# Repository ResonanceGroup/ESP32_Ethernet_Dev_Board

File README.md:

This project is meant to test 2 different ethernet controller chips for the ESP32. The board is testing the W5100S and W5500. Only populate one or the other. Feel free to use this schematic as a reference. Or make your dev board that includes the ethernet controllers. If referencing off of the schematic, please provide credit to the original project (this one).

Will update later which circuit performed the best.

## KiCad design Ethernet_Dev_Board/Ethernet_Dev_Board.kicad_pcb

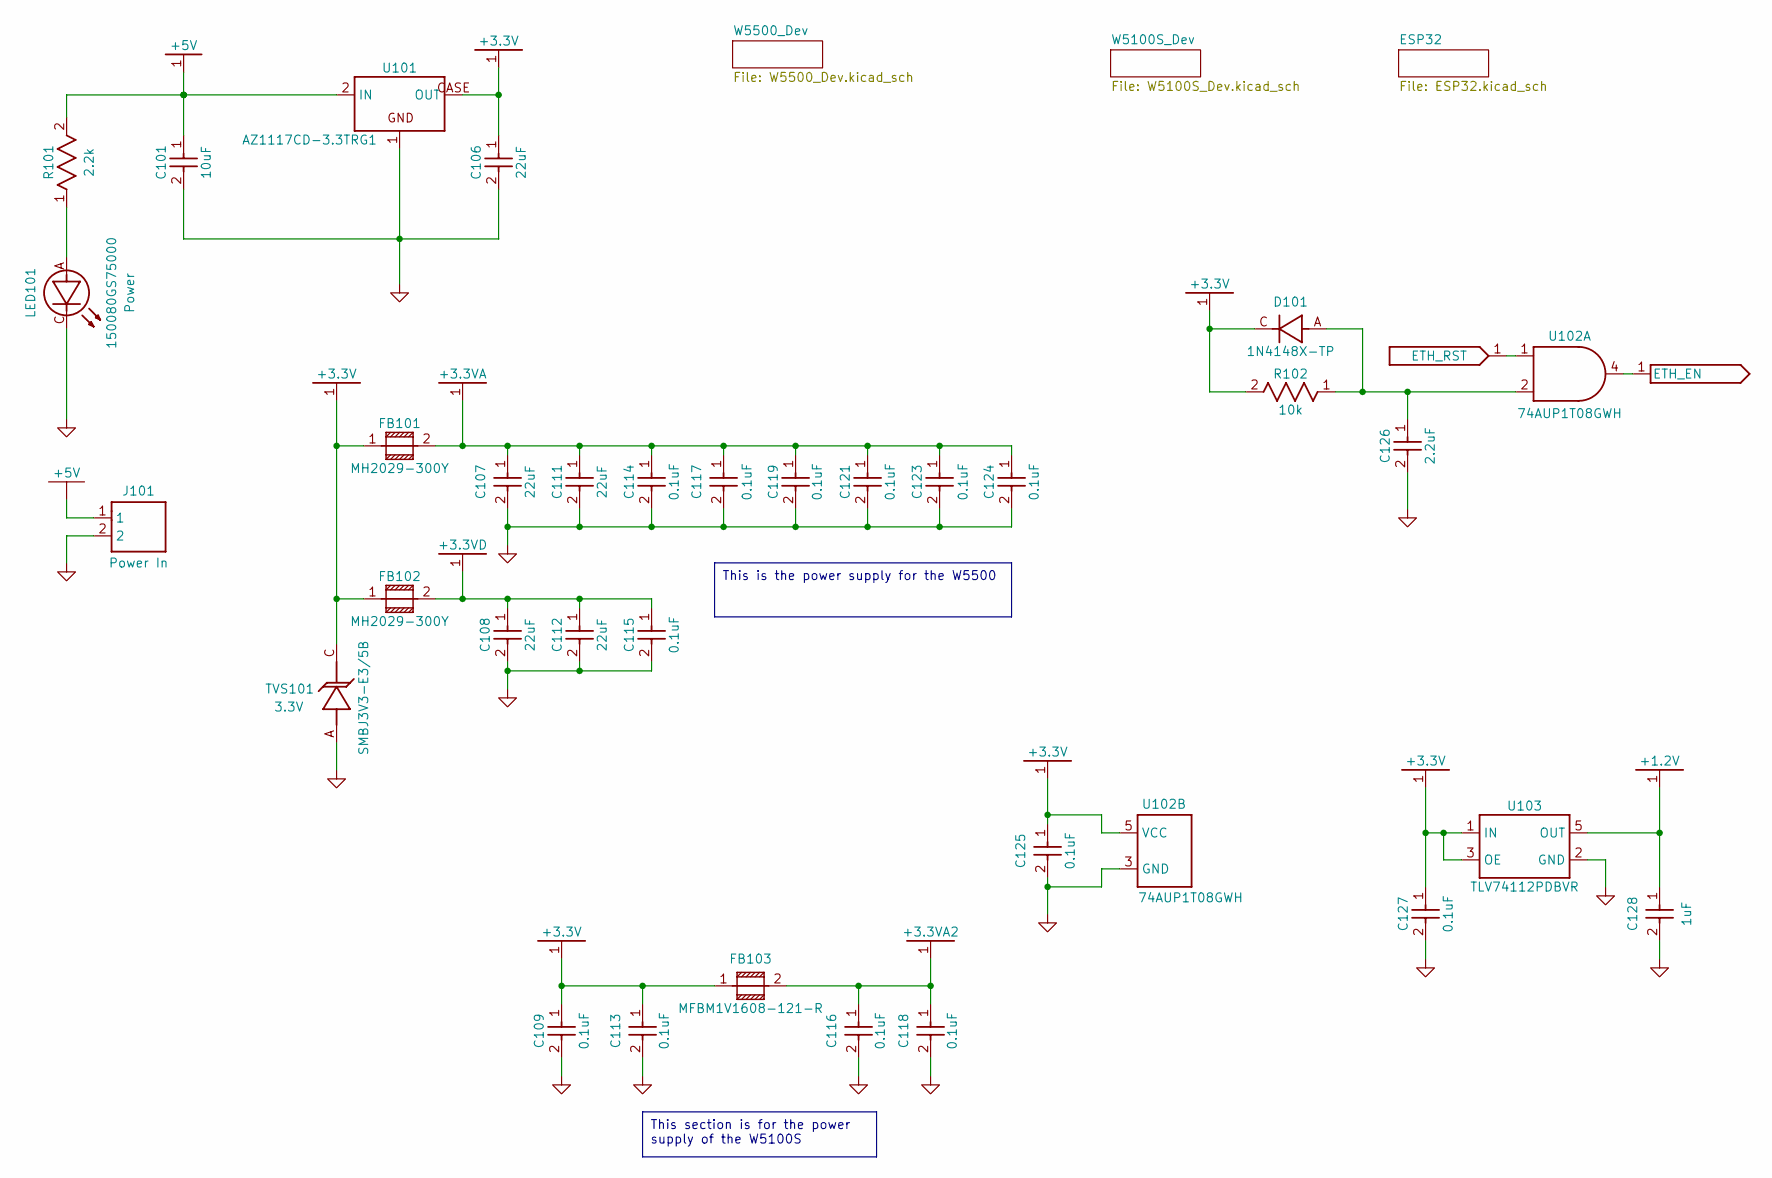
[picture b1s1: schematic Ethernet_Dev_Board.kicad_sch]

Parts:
C101: 10uF; 0603; Mfg. PN GRM188R61C106MA73D
C106, C107, C108, C111, C112: 22uF; 0603; Mfg. PN CL10A226MP8NUNE
C109, C113, C114, C115, C116, C117, C118, C119, C121, C123, C124, C125, C127: 0.1uF; 0603; Mfg. PN TMK107BJ104KA-T
C126: 2.2uF; 0603; Mfg. PN CL10A225KP8NNNC
C128: 1uF; 0603; Mfg. PN CL10B105KP8NFNC
D101: 1N4148X; SOD-523-D; Mfg. PN 1N4148X-TP
FB101, FB102: MH2029-300Y; 0805; Mfg. PN MH2029-300Y
FB103: 0603; Mfg. PN MFBM1V1608-121-R
J101: Power In; CUI_TBP01R1-508-02BE; Mfg. PN TBP01R1-508-02BE
LED101: Power; 0805-D; Mfg. PN 150080GS75000
R101: 2.2k; 0603; Mfg. PN RMCF0603FT2K20
R102: 10k; 0603; Mfg. PN RMCF0603FT10K0
TVS101: 3.3V; SMB-D; Mfg. PN SMBJ3V3-E3/5B
U101: AZ1117; TO252-3_(D-PAK); Mfg. PN AZ1117CD-3.3TRG1
U102: 74AUP1T08GWH; SOT23-5P65; Mfg. PN 74AUP1T08GWH
U103: 1.2V; SOT23-5P65; Mfg. PN TLV74112PDBVR

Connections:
+1.2V: C128.1, U103.5 (OUT); also elsewhere on the board
+3.3V: C106.1, C109.1, C113.1, C125.1, C127.1, D101.C, FB101.1, FB102.1, FB103.1, R102.2, TVS101.C (2), U101.CASE (OUT), U102.5 (VCC), U103.1 (IN), U103.3 (OE); also elsewhere on the board
+3.3VA: C107.1, C111.1, C114.1, C117.1, C119.1, C121.1, C123.1, C124.1, FB101.2; also elsewhere on the board
+3.3VA2: C116.1, C118.1, FB103.2; also elsewhere on the board
+3.3VD: C108.1, C112.1, C115.1, FB102.2; also elsewhere on the board
+5V: C101.1, J101.1, R101.2, U101.2 (IN); also elsewhere on the board
ETH_EN: U102.4 (Y); also elsewhere on the board
ETH_RST: U102.1 (A); also elsewhere on the board
GND1: C101.2, C106.2, C107.2, C108.2, C109.2, C111.2, C112.2, C113.2, C114.2, C115.2, C116.2, C117.2, C118.2, C119.2, C121.2, C123.2, C124.2, C125.2, C126.2, C127.2, C128.2, J101.2, LED101.C, TVS101.A (1), U101.1 (GND), U102.3 (GND), U103.2 (GND); also elsewhere on the board
unnamed: LED101.A, R101.1
unnamed: C126.1, D101.A, R102.1, U102.2 (C)

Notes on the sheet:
This is the power supply for the W5500
This section is for the power supply of the W5100S

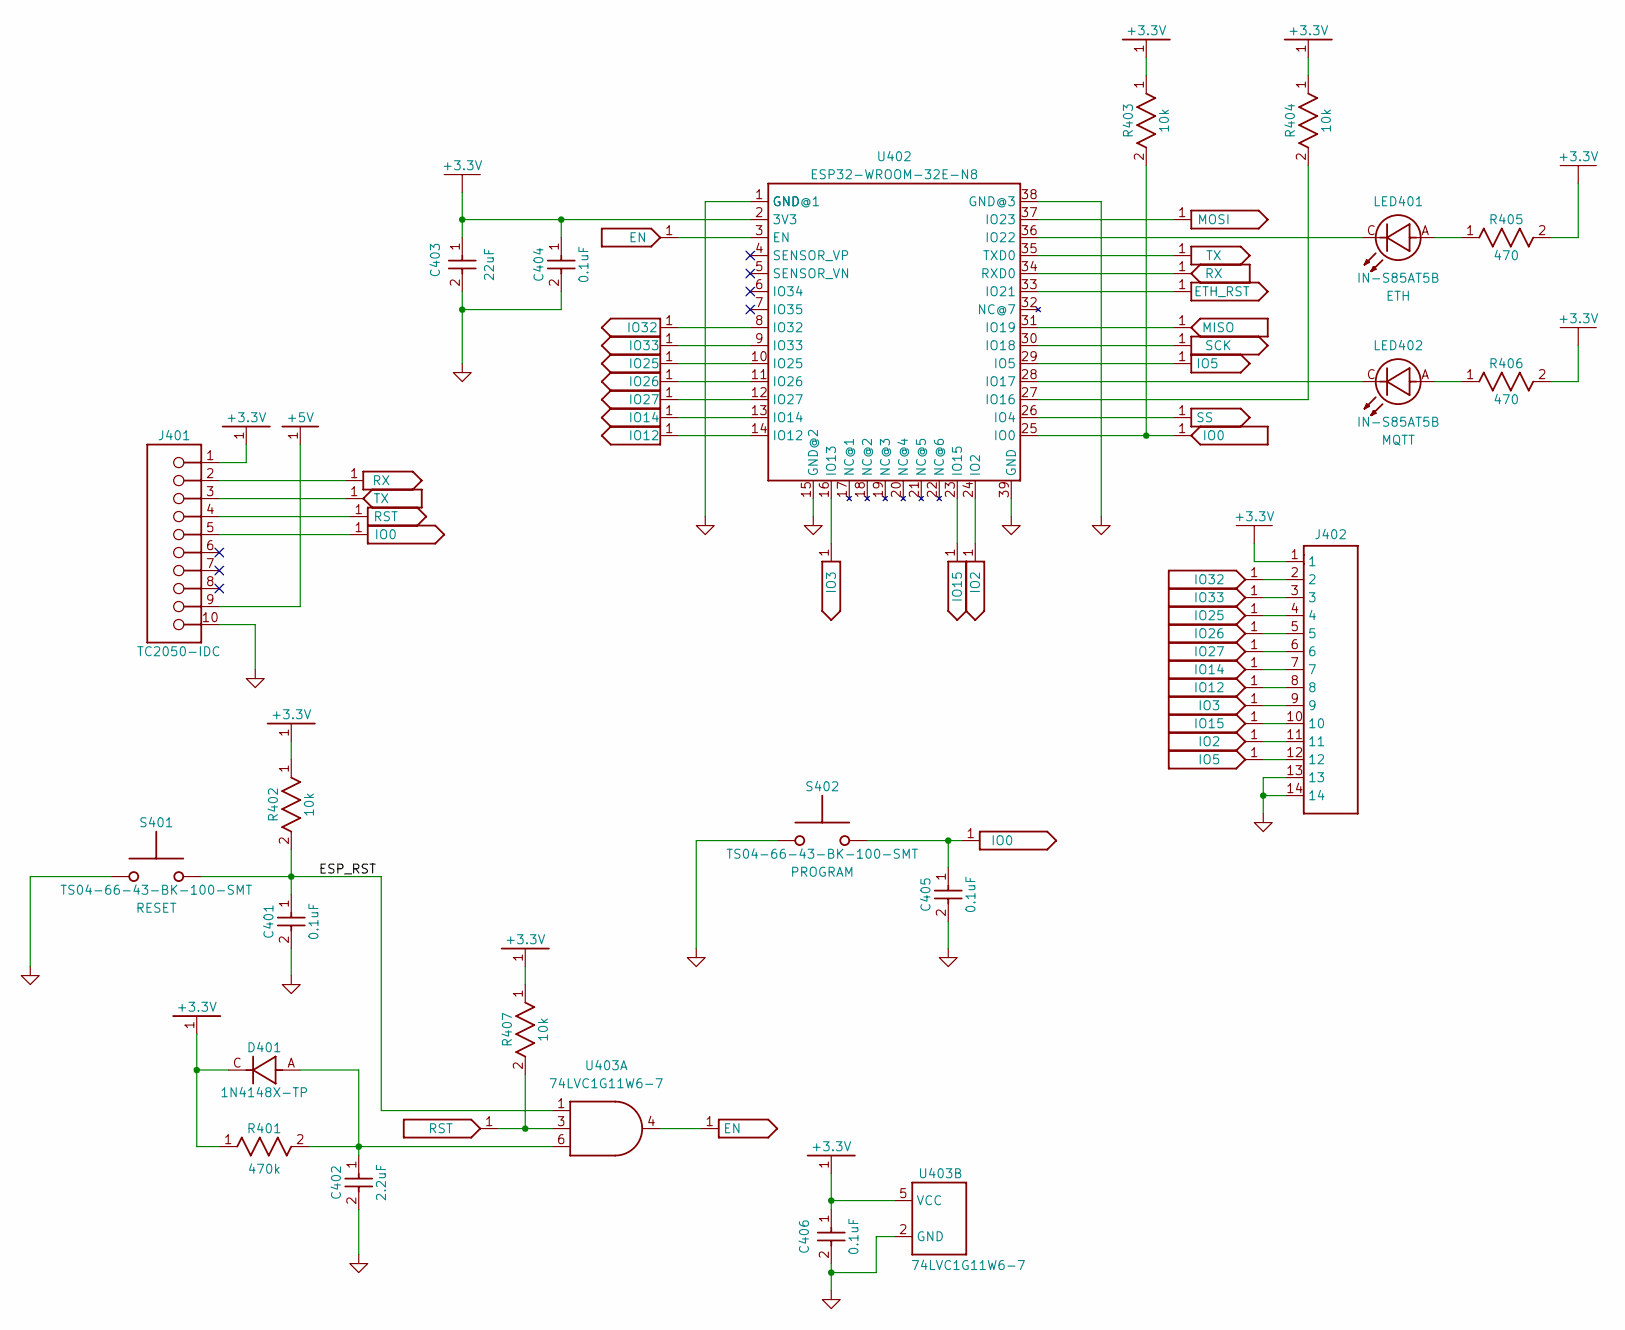
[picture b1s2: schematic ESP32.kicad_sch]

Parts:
C401, C404, C405, C406: 0.1uF; 0603; Mfg. PN TMK107BJ104KA-T
C402: 2.2uF; 0603; Mfg. PN CL10A225KP8NNNC
C403: 22uF; 0603; Mfg. PN CL10A226MP8NUNE
D401: 1N4148X; SOD-523-D; Mfg. PN 1N4148X-TP
J401: TAG-CONNECT_NL_10-POS_LEGS; TC2050-IDC; Mfg. PN TC2050-IDC
J402: PinHeader_1x14_P2.54mm_Vertical
LED401: ETH; 0805-D; Mfg. PN IN-S85AT5B
LED402: MQTT; 0805-D; Mfg. PN IN-S85AT5B
R401: 470k; 0603; Mfg. PN RMCF0603FT470K
R402, R403, R404, R407: 10k; 0603; Mfg. PN RMCF0603FT10K0
R405, R406: 470; 0603; Mfg. PN RMCF0603FT470R
S401: RESET; SW_TS04-66-65-BK-260-SMT; Mfg. PN TS04-66-43-BK-100-SMT
S402: PROGRAM; SW_TS04-66-65-BK-260-SMT; Mfg. PN TS04-66-43-BK-100-SMT
U402: ESP32-WROOM-32E; ESP32-WROOM_PCBANT; Mfg. PN ESP32-WROOM-32E-N8
U403: 74LVC1G11W6; SOT23-6; Mfg. PN 74LVC1G11W6-7

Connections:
+3.3V: C403.1, C404.1, C406.1, D401.C, J401.1, J402.1, R401.1, R402.1, R403.1, R404.1, R405.2, R406.2, R407.1, U402.2 (3V3), U403.5 (VCC); also elsewhere on the board
+5V: J401.9; also elsewhere on the board
/ESP32/ESP_RST: C401.1, R402.2, S401.1 (2), S401.3 (2), U403.1 (A)
EN: U402.3 (EN), U403.4 (Y)
ETH_RST: U402.33 (IO21); also elsewhere on the board
GND1: C401.2, C402.2, C403.2, C404.2, C405.2, C406.2, J401.10, J402.13, J402.14, S401.2 (1), S401.4 (1), S402.2 (1), S402.4 (1), U402.1 (GND), U402.15 (GND@2), U402.38 (GND@3), U402.39 (GND), U403.2 (GND); also elsewhere on the board
IO0: C405.1, J401.5, R403.2, S402.1 (2), S402.3 (2), U402.25 (IO0)
IO2: J402.11, U402.24 (IO2)
IO3: J402.9, U402.16 (IO13)
IO5: J402.12, U402.29 (IO5)
IO12: J402.8, U402.14 (IO12)
IO14: J402.7, U402.13 (IO14)
IO15: J402.10, U402.23 (IO15)
IO25: J402.4, U402.10 (IO25)
IO26: J402.5, U402.11 (IO26)
IO27: J402.6, U402.12 (IO27)
IO32: J402.2, U402.8 (IO32)
IO33: J402.3, U402.9 (IO33)
MISO: U402.31 (IO19); also elsewhere on the board
MOSI: U402.37 (IO23); also elsewhere on the board
unnamed: LED401.A, R405.1
unnamed: LED402.A, R406.1
unnamed: R404.2, U402.27 (IO16)
unnamed: LED402.C, U402.28 (IO17)
unnamed: LED401.C, U402.36 (IO22)
unnamed: C402.1, D401.A, R401.2, U403.6 (C)
RST: J401.4, R407.2, U403.3 (B)
RX: J401.2, U402.34 (RXD0)
SCK: U402.30 (IO18); also elsewhere on the board
SS: U402.26 (IO4); also elsewhere on the board
TX: J401.3, U402.35 (TXD0)

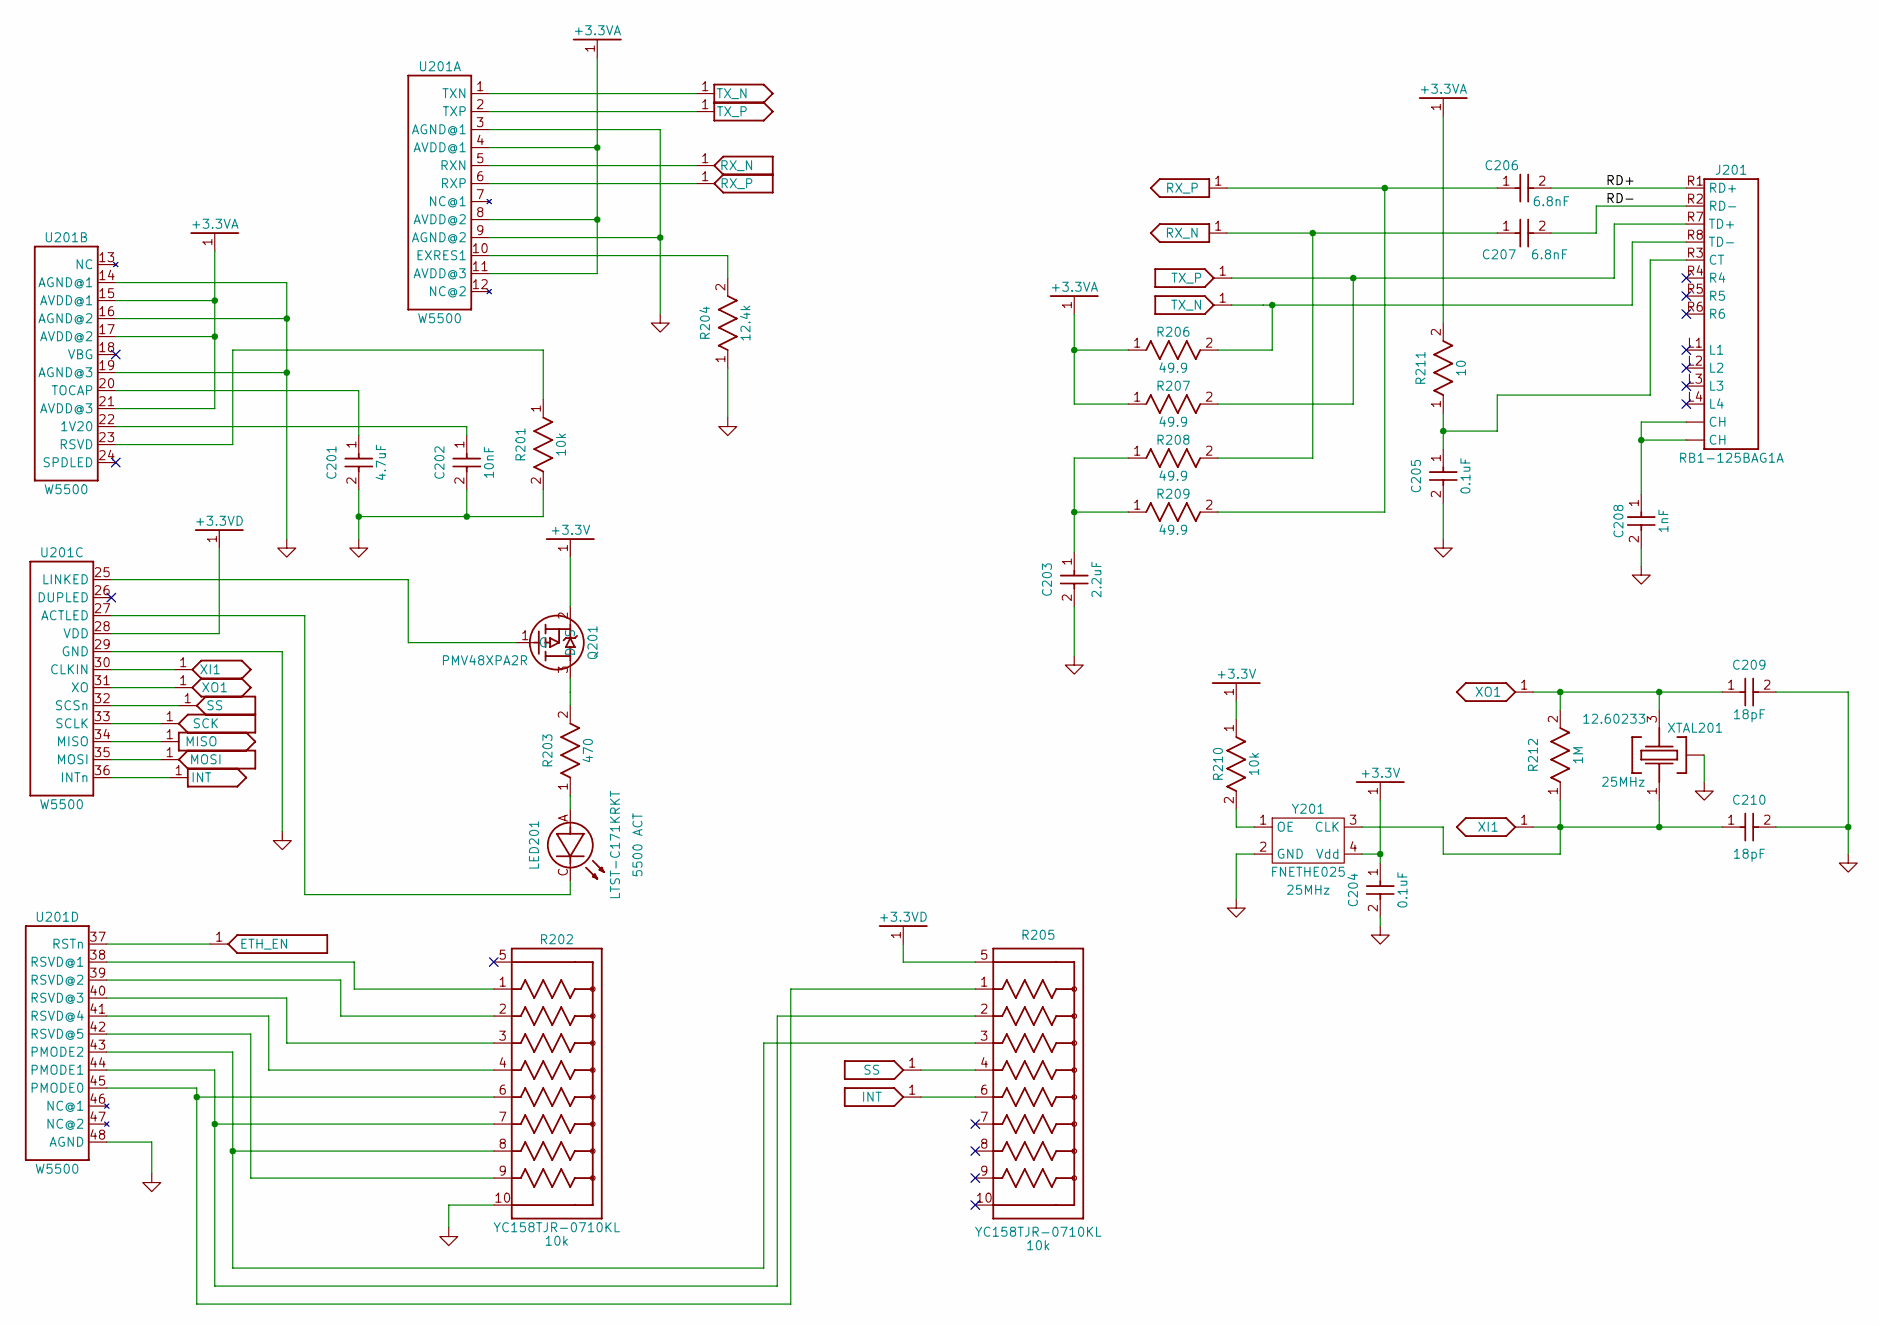
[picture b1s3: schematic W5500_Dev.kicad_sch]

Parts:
C201: 4.7uF; 0603; Mfg. PN CL10A475KP8NNNC
C202: 10nF; 0603; Mfg. PN GRM1885C1H103JA01J
C203: 2.2uF; 0603; Mfg. PN CL10A225KP8NNNC
C204, C205: 0.1uF; 0603; Mfg. PN TMK107BJ104KA-T
C206, C207: 6.8nF; 0603; Mfg. PN C1608C0G2A682J080AC
C208: 1nF; 1206; Mfg. PN C1206C102KGRAC7800
C209, C210: 18pF; 0603; Mfg. PN CML0603C0G180JT50V
J201: WIZNET_RB1-125BAG1A; Mfg. PN RB1-125BAG1A
LED201: 5500 ACT; 0805-D; Mfg. PN LTST-C171KRKT
Q201: PMV48XPA2R; SOT23-3P95; Mfg. PN PMV48XPA2R
R201, R210: 10k; 0603; Mfg. PN RMCF0603FT10K0
R202, R205: 10k; RESCAXS10P64_1206; Mfg. PN YC158TJR-0710KL
R203: 470; 0603; Mfg. PN RMCF0603FT470R
R204: 12.4k; 0603; Mfg. PN RMCF0603FT12K4
R206, R207, R208, R209: 49.9; 0603; Mfg. PN RMCF0603FT49R9
R211: 10; 0603; Mfg. PN RMCF0603FT10R0
R212: 1M; 0603; Mfg. PN RMCF0603FG1M00
U201: WIZNET_W5500; QFP48P50; Mfg. PN W5500
XTAL201: 25MHz; YANGXING_SMD_3225_4L; Mfg. PN 12.60233
Y201: 25MHz; Crystal_SMD_4Pin_7.0mmx5.0mm; Mfg. PN FNETHE025

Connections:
+3.3V: C204.1, Q201.2 (S), R210.1, Y201.4 (Vdd); also elsewhere on the board
+3.3VA: R206.1, R207.1, R211.2, U201.4 (AVDD@1), U201.8 (AVDD@2), U201.11 (AVDD@3), U201.15 (AVDD@1), U201.17 (AVDD@2), U201.21 (AVDD@3); also elsewhere on the board
+3.3VD: R205.5 (1@1), U201.28 (VDD); also elsewhere on the board
/W5500_Dev/RD+: C206.2, J201.R1 (RD+)
/W5500_Dev/RD-: C207.2, J201.R2 (RD-)
ETH_EN: U201.37 (RSTn); also elsewhere on the board
GND1: C201.2, C202.2, C203.2, C204.2, C205.2, C208.2, C209.2, C210.2, R201.2, R202.10 (1@2), R204.1, U201.3 (AGND@1), U201.9 (AGND@2), U201.14 (AGND@1), U201.16 (AGND@2), U201.19 (AGND@3), U201.29 (GND), U201.48 (AGND), XTAL201.2 (3@2), Y201.2 (GND); also elsewhere on the board
INT: R205.6, U201.36 (INTn)
MISO: U201.34 (MISO); also elsewhere on the board
MOSI: U201.35 (MOSI); also elsewhere on the board
unnamed: C203.1, R208.1, R209.1
unnamed: C208.1, J201.S1 (CH), J201.S2 (CH)
unnamed: C205.1, J201.R3 (CT), R211.1
unnamed: LED201.A, R203.1
unnamed: Q201.3 (D), R203.2
unnamed: Q201.1 (G), U201.25 (LINKED)
unnamed: R202.1 (2), U201.38 (RSVD@1)
unnamed: R202.2 (3), U201.39 (RSVD@2)
unnamed: R202.3 (4), U201.40 (RSVD@3)
unnamed: R202.4 (5), U201.41 (RSVD@4)
unnamed: R202.6, R205.1 (2), U201.45 (PMODE0)
unnamed: R202.7, R205.2 (3), U201.44 (PMODE1)
unnamed: R202.8, R205.3 (4), U201.43 (PMODE2)
unnamed: R204.2, U201.10 (EXRES1)
unnamed: C202.1, U201.22 (1V20)
unnamed: R201.1, U201.23 (RSVD)
unnamed: C201.1, U201.20 (TOCAP)
unnamed: LED201.C, U201.27 (ACTLED)
unnamed: R202.9, U201.42 (RSVD@5)
unnamed: R210.2, Y201.1 (OE)
RX_N: C207.1, R208.2, U201.5 (RXN)
RX_P: C206.1, R209.2, U201.6 (RXP)
SCK: U201.33 (SCLK); also elsewhere on the board
SS: R205.4 (5), U201.32 (SCSn); also elsewhere on the board
TX_N: J201.R8 (TD-), R206.2, U201.1 (TXN)
TX_P: J201.R7 (TD+), R207.2, U201.2 (TXP)
XI1: C210.1, R212.1, U201.30 (CLKIN), XTAL201.1, Y201.3 (CLK)
XO1: C209.1, R212.2, U201.31 (XO), XTAL201.3 (3@1)

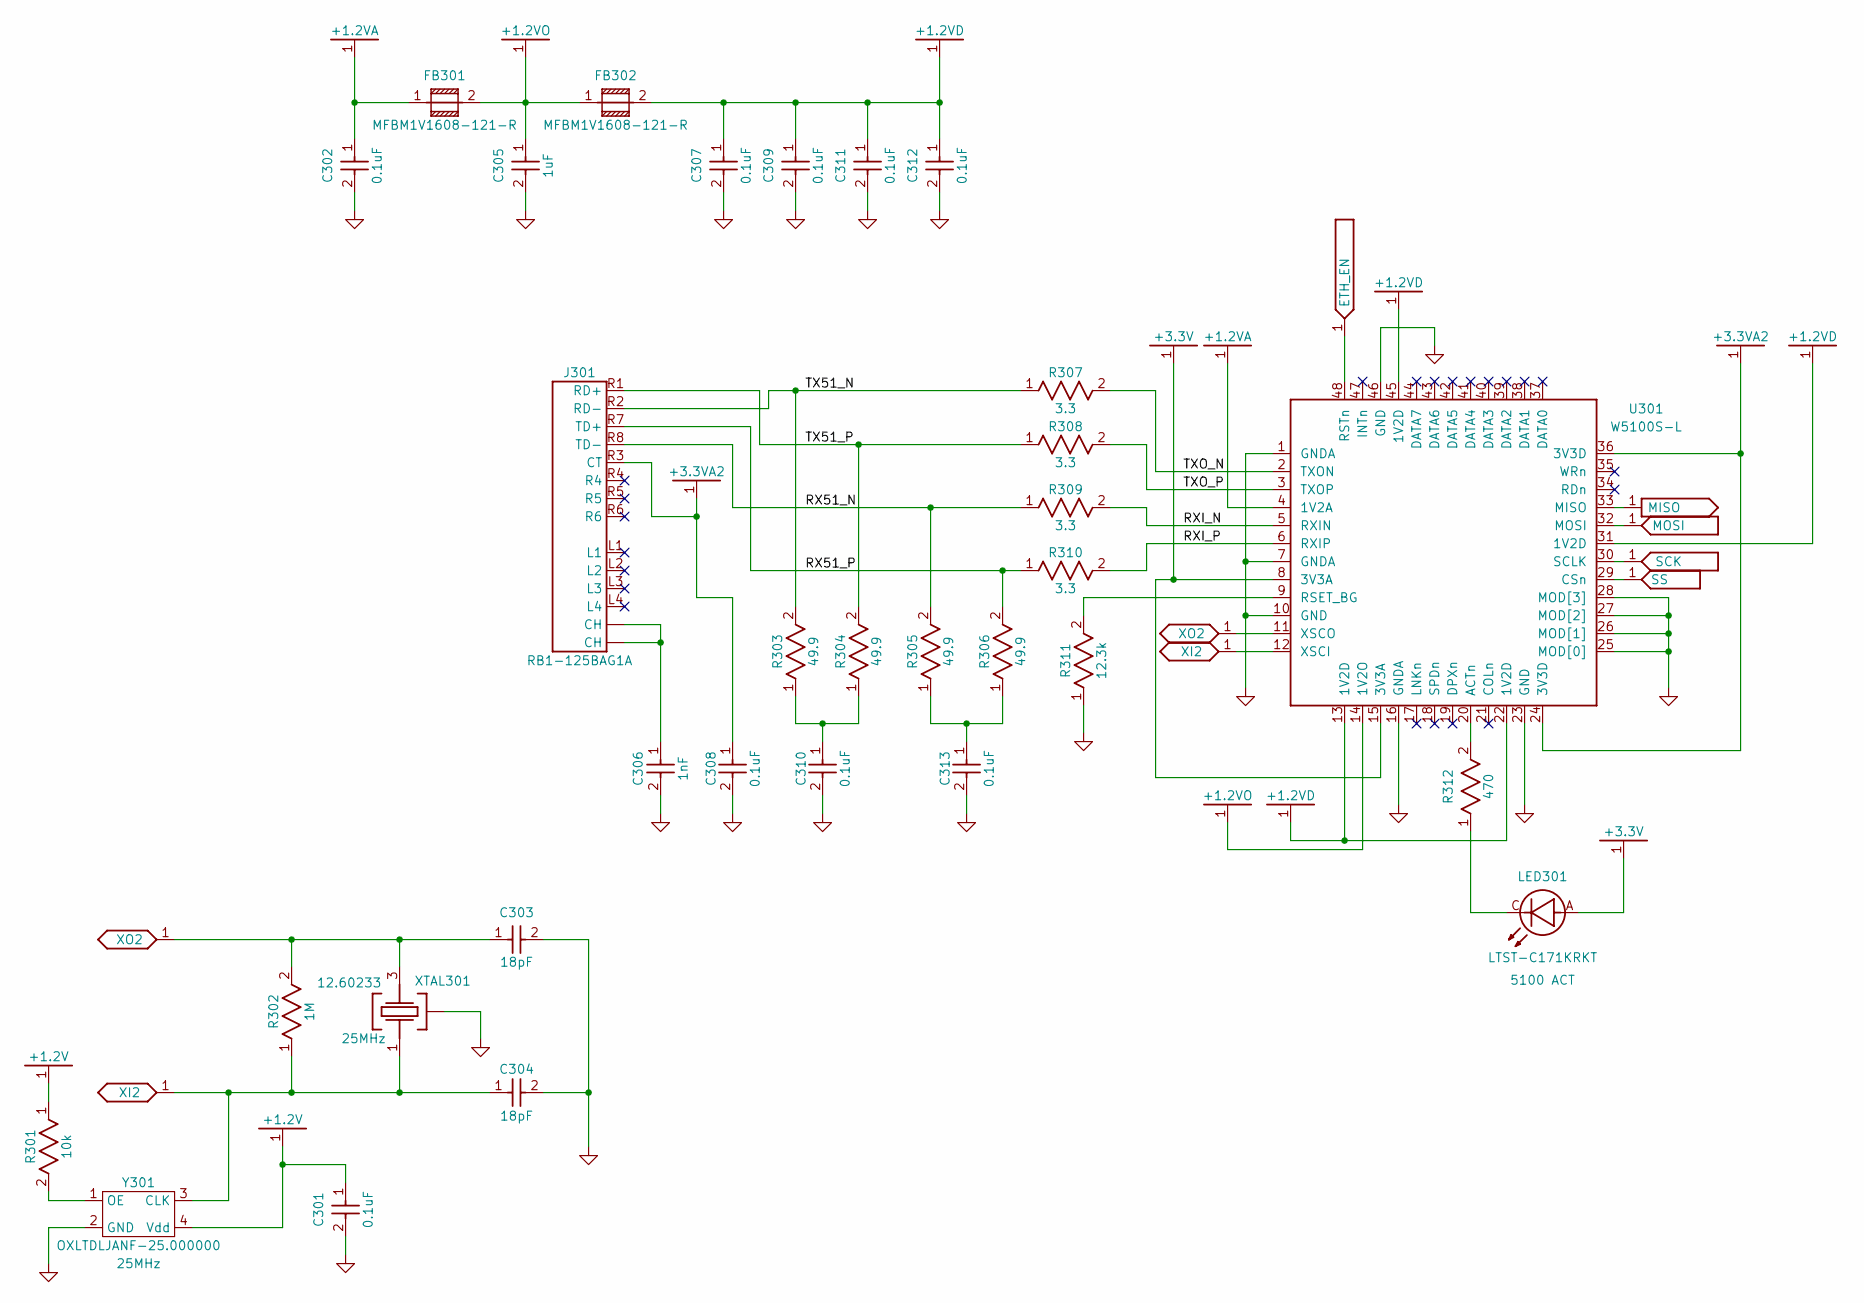
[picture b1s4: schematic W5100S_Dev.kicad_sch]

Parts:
C301, C302, C307, C308, C309, C310, C311, C312, C313: 0.1uF; 0603; Mfg. PN TMK107BJ104KA-T
C303, C304: 18pF; 0603; Mfg. PN CML0603C0G180JT50V
C305: 1uF; 0603; Mfg. PN CL10B105KP8NFNC
C306: 1nF; 1206; Mfg. PN C1206C102KGRAC7800
FB301, FB302: 0603; Mfg. PN MFBM1V1608-121-R
J301: WIZNET_RB1-125BAG1A; Mfg. PN RB1-125BAG1A
LED301: 5100 ACT; 0805-D; Mfg. PN LTST-C171KRKT
R301: 10k; 0603; Mfg. PN RMCF0603FT10K0
R302: 1M; 0603; Mfg. PN RMCF0603FG1M00
R303, R304, R305, R306: 49.9; 0603; Mfg. PN RMCF0603FT49R9
R307, R308, R309, R310: 3.3; 0603; Mfg. PN RMCF0603JT3R30
R311: 12.3k; 0603; Mfg. PN RT0603BRD0712K3L
R312: 470; 0603; Mfg. PN RMCF0603FT470R
U301: QFP48P50; Mfg. PN W5100S-L
XTAL301: 25MHz; YANGXING_SMD_3225_4L; Mfg. PN 12.60233
Y301: 25MHz; Crystal_SMD_4Pin_3.2x2.5mm; Mfg. PN OXLTDLJANF-25.000000

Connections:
+1.2V: C301.1, R301.1, Y301.4 (Vdd); also elsewhere on the board
+1.2VA: C302.1, FB301.1, U301.4 (1V2A)
+1.2VD: C307.1, C309.1, C311.1, C312.1, FB302.2, U301.13 (1V2D), U301.22 (1V2D), U301.31 (1V2D), U301.45 (1V2D)
+1.2VO: C305.1, FB301.2, FB302.1, U301.14 (1V2O)
+3.3V: LED301.A, U301.8 (3V3A), U301.15 (3V3A); also elsewhere on the board
+3.3VA2: C308.1, J301.R3 (CT), U301.24 (3V3D), U301.36 (3V3D); also elsewhere on the board
/W5100S_Dev/RX51_N: J301.R8 (TD-), R305.2, R309.1
/W5100S_Dev/RX51_P: J301.R7 (TD+), R306.2, R310.1
/W5100S_Dev/RXI_N: R309.2, U301.5 (RXIN)
/W5100S_Dev/RXI_P: R310.2, U301.6 (RXIP)
/W5100S_Dev/TX51_N: J301.R2 (RD-), R303.2, R307.1
/W5100S_Dev/TX51_P: J301.R1 (RD+), R304.2, R308.1
/W5100S_Dev/TXO_N: R307.2, U301.2 (TXON)
/W5100S_Dev/TXO_P: R308.2, U301.3 (TXOP)
ETH_EN: U301.48 (RSTn); also elsewhere on the board
GND1: C301.2, C302.2, C303.2, C304.2, C305.2, C306.2, C307.2, C308.2, C309.2, C310.2, C311.2, C312.2, C313.2, R311.1, U301.1 (GNDA), U301.7 (GNDA), U301.10 (GND), U301.16 (GNDA), U301.23 (GND), U301.25 (MOD[0]), U301.26 (MOD[1]), U301.27 (MOD[2]), U301.28 (MOD[3]), U301.46 (GND), XTAL301.2 (CASE), Y301.2 (GND); also elsewhere on the board
MISO: U301.33 (MISO); also elsewhere on the board
MOSI: U301.32 (MOSI); also elsewhere on the board
unnamed: C306.1, J301.S1 (CH), J301.S2 (CH)
unnamed: C310.1, R303.1, R304.1
unnamed: C313.1, R305.1, R306.1
unnamed: LED301.C, R312.1
unnamed: R312.2, U301.20 (ACTn)
unnamed: R311.2, U301.9 (RSET_BG)
unnamed: R301.2, Y301.1 (OE)
SCK: U301.30 (SCLK); also elsewhere on the board
SS: U301.29 (CSn); also elsewhere on the board
XI2: C304.1, R302.1, U301.12 (XSCI), XTAL301.1, Y301.3 (CLK)
XO2: C303.1, R302.2, U301.11 (XSCO), XTAL301.3 (3@1)

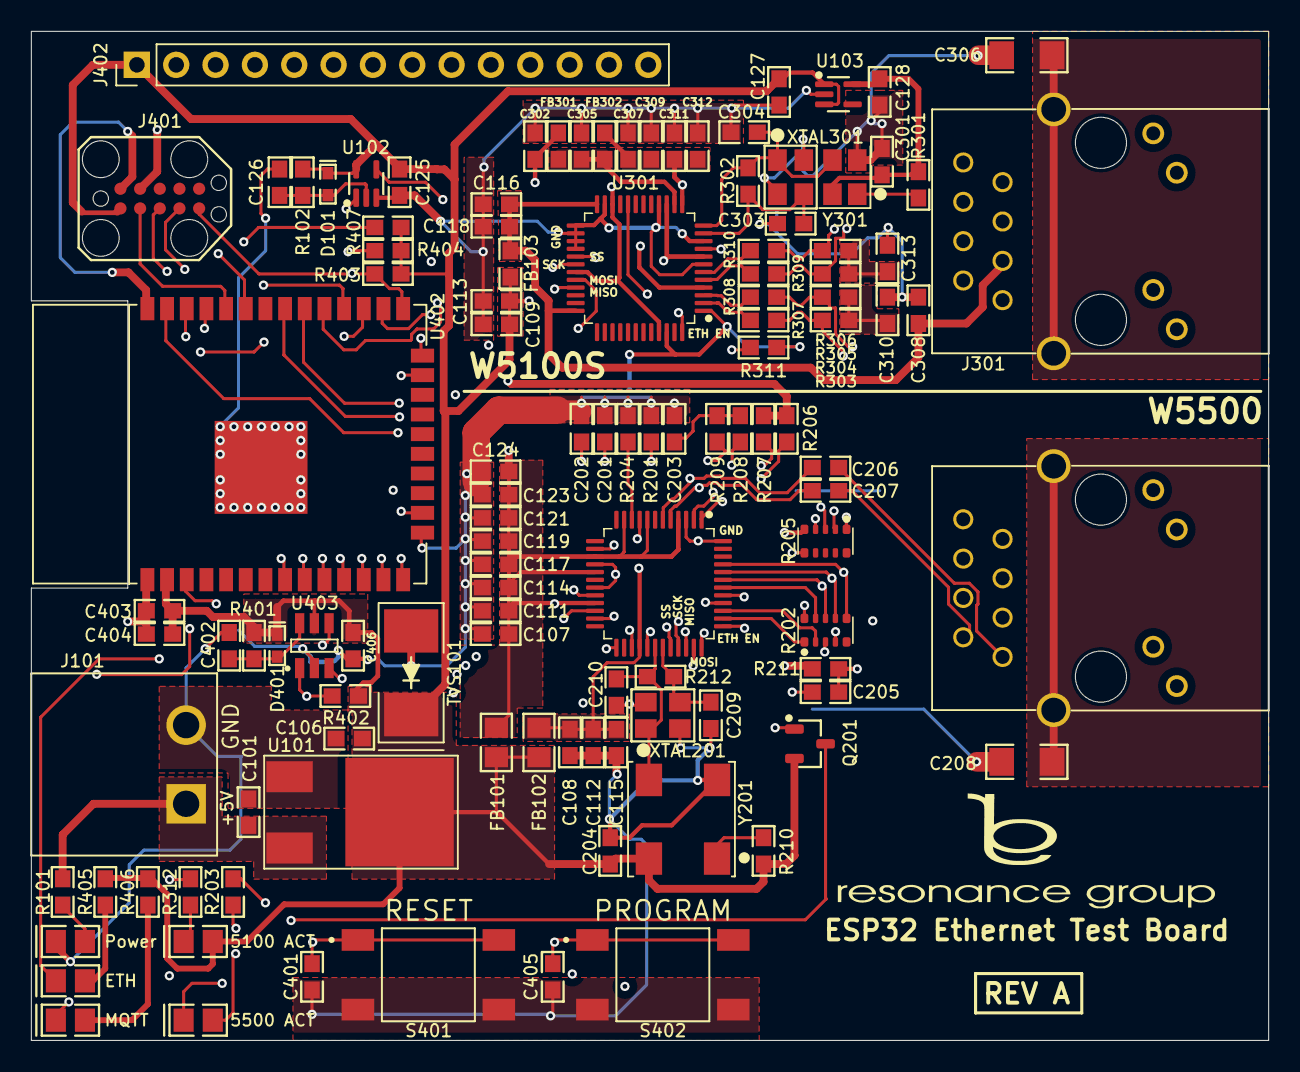
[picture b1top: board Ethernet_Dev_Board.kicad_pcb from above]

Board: 4 copper layers, 79.9 x 65.2 mm, 115 parts (0 on the bottom side), 87 nets.

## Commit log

2024-03-13 Generated PCB file from schematic
2024-03-14 Added notes to schematics for changes
2024-03-14 Associating footprint to component
2024-03-14 Added TVS diode and redid the LED circuit on the ESP32
2024-03-14 Updated notes in schematic
2024-03-14 Added in 1.2 V regulator and broke out unused IO pins to header
2024-03-14 Net adjustments. Beginning board layout
2024-03-15 Initial component placement
2024-03-15 Removed 1 TVS diode. removed 1 reset circuit. Placed Ethernet port in both W5500 and W5100S circuits
2024-03-16 Removed unnecessary nets. Beginning board routing
2024-03-16 Finished first version of routing the board. Also adjusted some nets
2024-03-18 Minor updates
2024-03-18 Converted Board into 4 layers
2024-03-18 Fixed DRC errors. Edited layout stack
2024-03-18 Rev A Design files finish
2024-03-18 Added ordering BOM for REV A
2024-03-19 Added RG logo
2024-03-19 Adjusted RG logo
2024-03-19 Small adjustment
2024-03-19 Created Updated gerber files
2024-03-20 Fixed an issue with a footprint that had height and width of 0,0
2024-03-20 Last update before sending out to fabrication
2024-03-20 Added readme
2024-03-21 Updated part(s) due to out of stock
2024-03-28 Added in firmware needed to run the test board
2024-03-28 Hiding important sercets
2024-09-11 Changed cap value to 2.2 and changed SS pin
